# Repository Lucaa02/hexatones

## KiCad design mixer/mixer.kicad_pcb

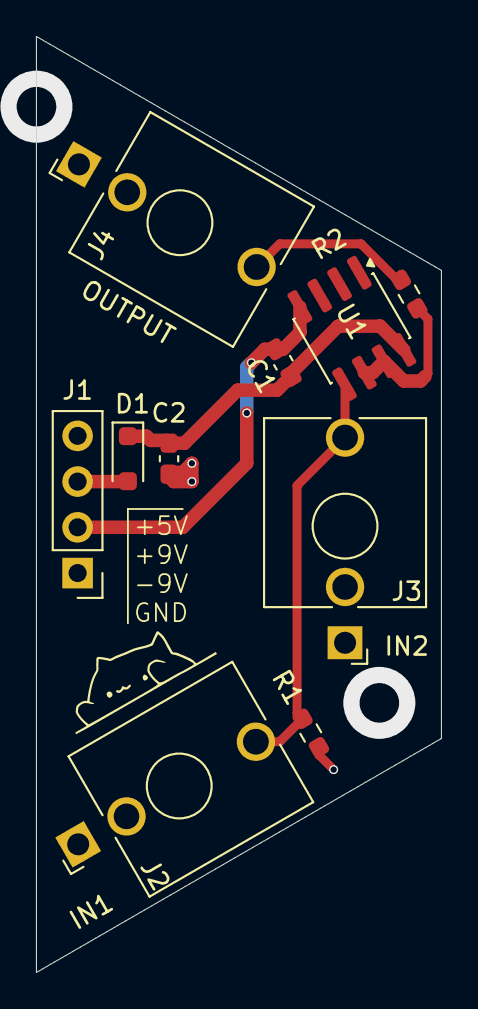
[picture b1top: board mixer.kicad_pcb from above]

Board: 2 copper layers, 22.5 x 52.0 mm, 10 parts (0 on the bottom side), 7 nets.

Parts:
C1: 100n; C_0603_1608Metric_Pad1.08x0.95mm_HandSolder
C2: 10u; C_0603_1608Metric_Pad1.08x0.95mm_HandSolder
D1: D_Schottky; D_SOD-323_HandSoldering
J1: INPUT; PinHeader_1x04_P2.54mm_Vertical
J2, J3, J4: NJ2FD-V; Jack_3.5mm_QingPu_WQP-PJ398SM_Vertical_CircularHoles
R1: 100k; R_0603_1608Metric_Pad0.98x0.95mm_HandSolder
R2: 1k; R_0603_1608Metric_Pad0.98x0.95mm_HandSolder
U1: TL072; SOIC-8_3.9x4.9mm_P1.27mm

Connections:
0: C2.2, J1.1, J2.S, J3.S, J4.S, R1.1
/Vin_minus: C1.2, J1.2, U1.4 (V-)
/Vin_plus: C1.1, C2.1, D1.1 (K), U1.8 (V+)
unnamed: D1.2 (A), J1.3
unnamed: J4.T, R2.1
unnamed: J2.T, J3.T, R1.2, U1.5 (+)
unnamed: R2.2, U1.6 (-), U1.7
